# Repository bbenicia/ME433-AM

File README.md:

# ME433-AM
ME 433 Advanced Mechatronics Spring 2022

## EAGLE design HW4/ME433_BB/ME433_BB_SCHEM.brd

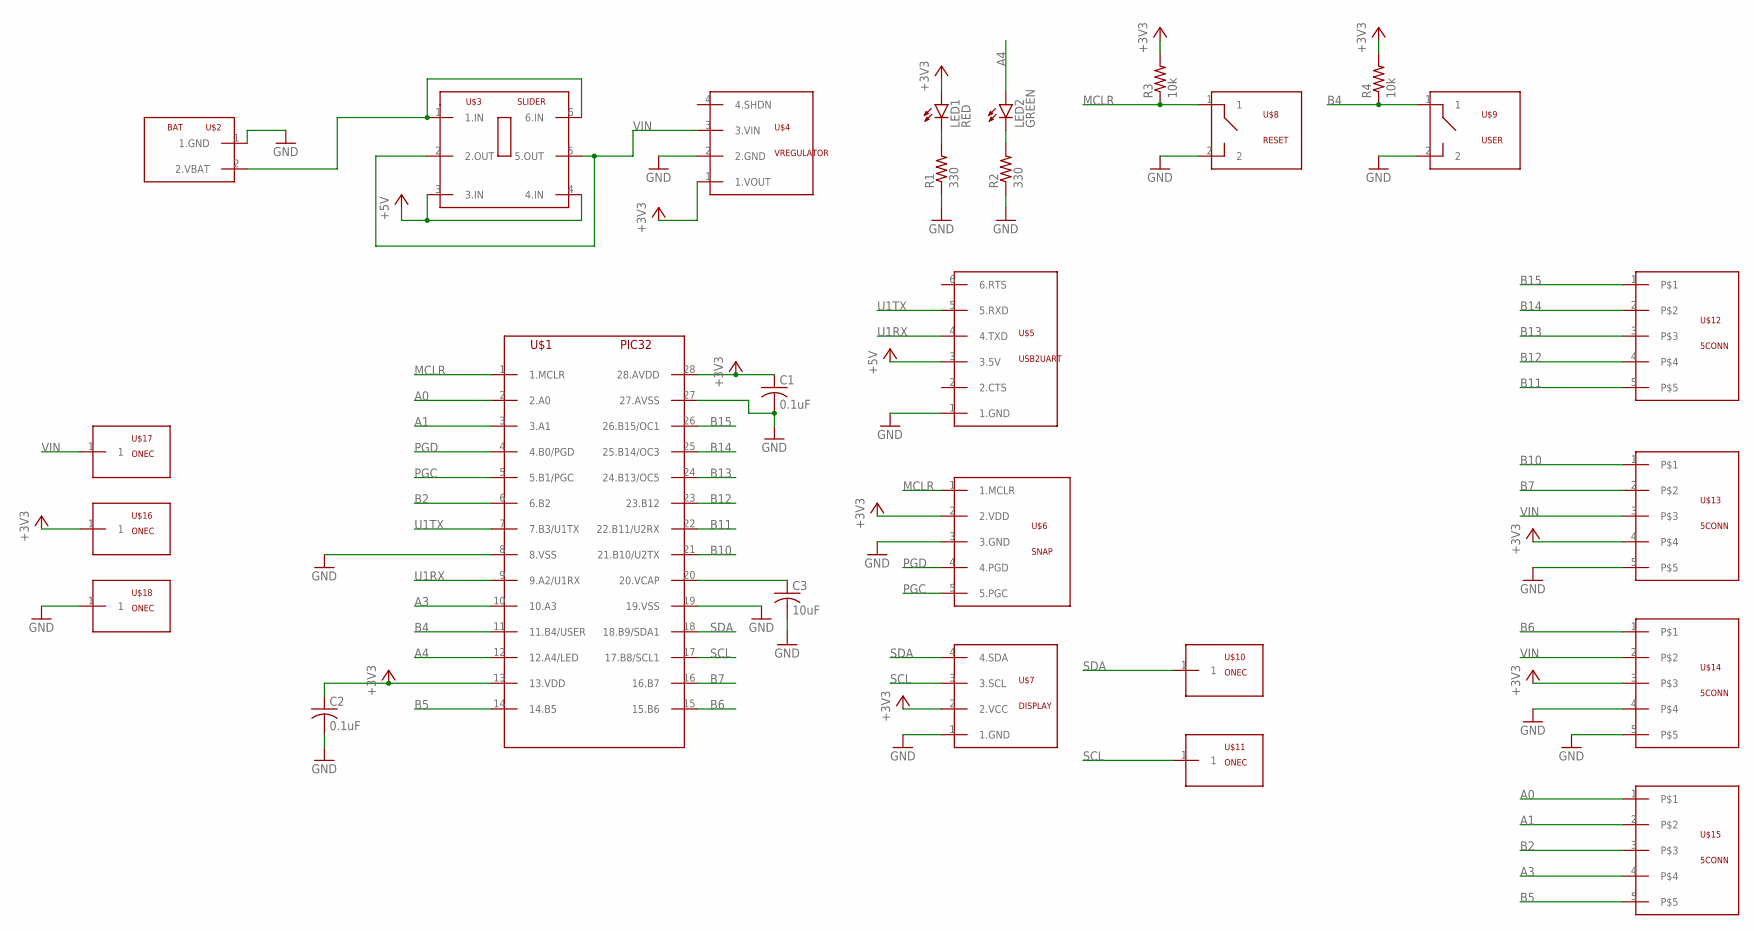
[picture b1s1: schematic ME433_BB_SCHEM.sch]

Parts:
C1, C2: 0.1uF; C025-024X044
C3: 10uF; C025-024X044
LED1: RED; LED3MM
LED2: GREEN; LED3MM
R1, R2: 330; 0207/7
R3, R4: 10k; 0207/7
U$1: PIC32; DIL28-3
U$2: BAT
U$3: SLIDER
U$4: VREGULATOR
U$5: USB2UART
U$6: SNAP
U$7: DISPLAY
U$8: RESET; BUTT
U$9: USER; BUTT
U$10, U$11, U$16, U$17, U$18: ONEC
U$12, U$13, U$14, U$15: 5CONN

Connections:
+3V3: C1.1, C2.1, LED1.A, R3.2, R4.2, U$1.13 (13.VDD), U$1.28 (28.AVDD), U$4.1 (1.VOUT), U$6.2 (2.VDD), U$7.2 (2.VCC), U$13.4, U$14.3, U$16.1
+5V: U$3.3 (3.IN), U$3.4 (4.IN), U$5.3 (3.5V)
A0: U$1.2 (2.A0), U$15.1
A1: U$1.3 (3.A1), U$15.2
A3: U$1.10 (10.A3), U$15.4
A4: LED2.A, U$1.12 (12.A4/LED)
B2: U$1.6 (6.B2), U$15.3
B4: R4.1, U$1.11 (11.B4/USER), U$9.1
B5: U$1.14 (14.B5), U$15.5
B6: U$1.15 (15.B6), U$14.1
B7: U$1.16 (16.B7), U$13.2
B10: U$1.21 (21.B10/U2TX), U$13.1
B11: U$1.22 (22.B11/U2RX), U$12.5
B12: U$1.23 (23.B12), U$12.4
B13: U$1.24 (24.B13/OC5), U$12.3
B14: U$1.25 (25.B14/OC3), U$12.2
B15: U$1.26 (26.B15/OC1), U$12.1
GND: C1.2, C2.2, C3.2, R1.1, R2.1, U$1.8 (8.VSS), U$1.19 (19.VSS), U$1.27 (27.AVSS), U$2.1 (1.GND), U$4.2 (2.GND), U$5.1 (1.GND), U$6.3 (3.GND), U$7.1 (1.GND), U$8.2, U$9.2, U$13.5, U$14.4, U$14.5, U$18.1
MCLR: R3.1, U$1.1 (1.MCLR), U$6.1 (1.MCLR), U$8.1
unnamed: LED1.K (C), R1.2
unnamed: U$2.2 (2.VBAT), U$3.1 (1.IN), U$3.6 (6.IN)
unnamed: LED2.K (C), R2.2
unnamed: C3.1, U$1.20 (20.VCAP)
PGC: U$1.5 (5.B1/PGC), U$6.5 (5.PGC)
PGD: U$1.4 (4.B0/PGD), U$6.4 (4.PGD)
SCL: U$1.17 (17.B8/SCL1), U$7.3 (3.SCL), U$11.1
SDA: U$1.18 (18.B9/SDA1), U$7.4 (4.SDA), U$10.1
U1RX: U$1.9 (9.A2/U1RX), U$5.4 (4.TXD)
U1TX: U$1.7 (7.B3/U1TX), U$5.5 (5.RXD)
VIN: U$3.2 (2.OUT), U$3.5 (5.OUT), U$4.3 (3.VIN), U$13.3, U$14.2, U$17.1

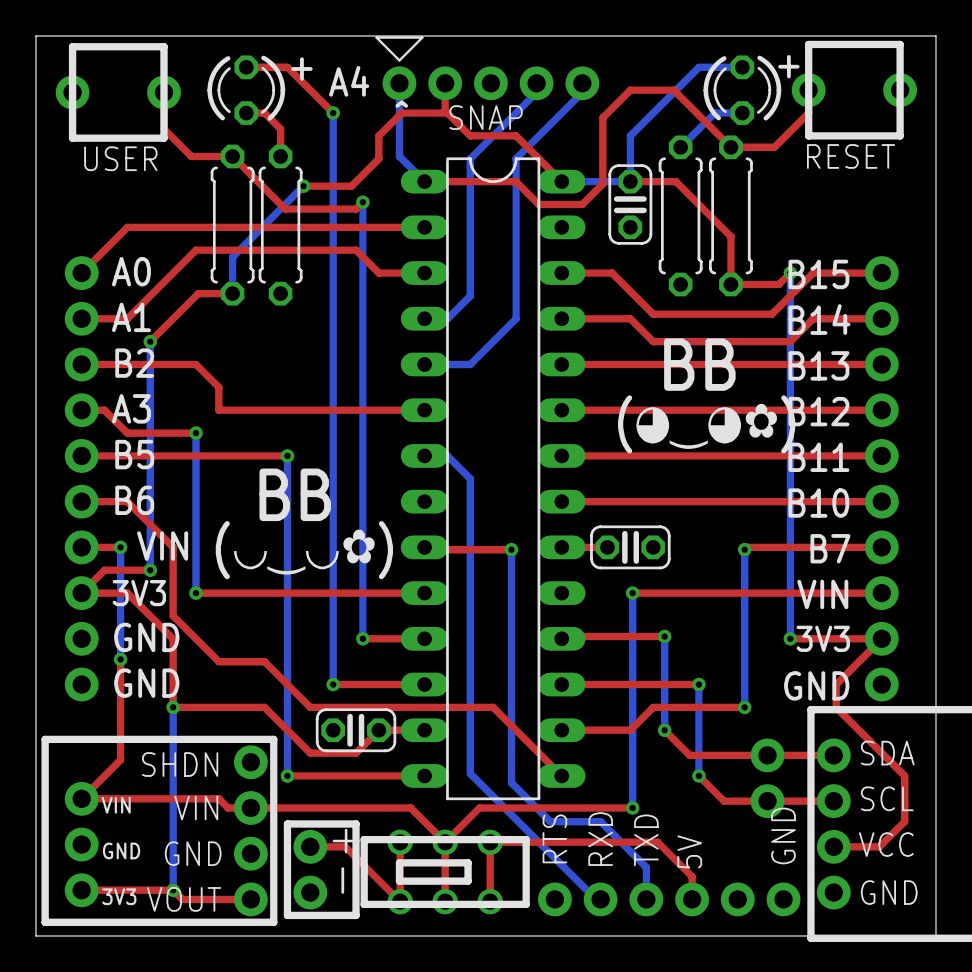
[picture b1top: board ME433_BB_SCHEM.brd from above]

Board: 2 copper layers, 50.0 x 50.0 mm, 27 parts (0 on the bottom side), 30 nets.

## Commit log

2022-04-05 Hw 2 mplabx
    Hw 2 project file and main.c code
2022-04-05 circuit picture drawing
    picture of drawn circuit diagram
2022-04-05 circuit picture
    circuit picture physical
2022-04-06 HW 3 PIC project folder
    pic folder with code
2022-04-14 EAGLE PROJECT
    eagle files,, schematic and board layout images, gerber files, etc , etc
2022-04-19 hw 5
    hw 5 folder and code
2022-04-20 HW 5 more code
    more code added ,almost done
2022-04-21 finalized code
    fixed triangle wave equation , fixed some other bugs ,etc
2022-04-21 wave pictures
    pictures
2022-04-27 HW 6 upload
    finished hw 6 code
2022-05-15 HW 7
    homework 7
2022-05-16 HW 8
    finished hw 8
2022-05-24 HW 9
    HW 9 neopixel new version up and running
2022-05-25 HW10
    HW 10 python , pic , mu circuitpython trial
2022-05-25 addition
    addition
2022-06-01 hw 11
    hw 11 , pictures and pico
2022-06-12 HW 12 cad
    hw 12 cad
